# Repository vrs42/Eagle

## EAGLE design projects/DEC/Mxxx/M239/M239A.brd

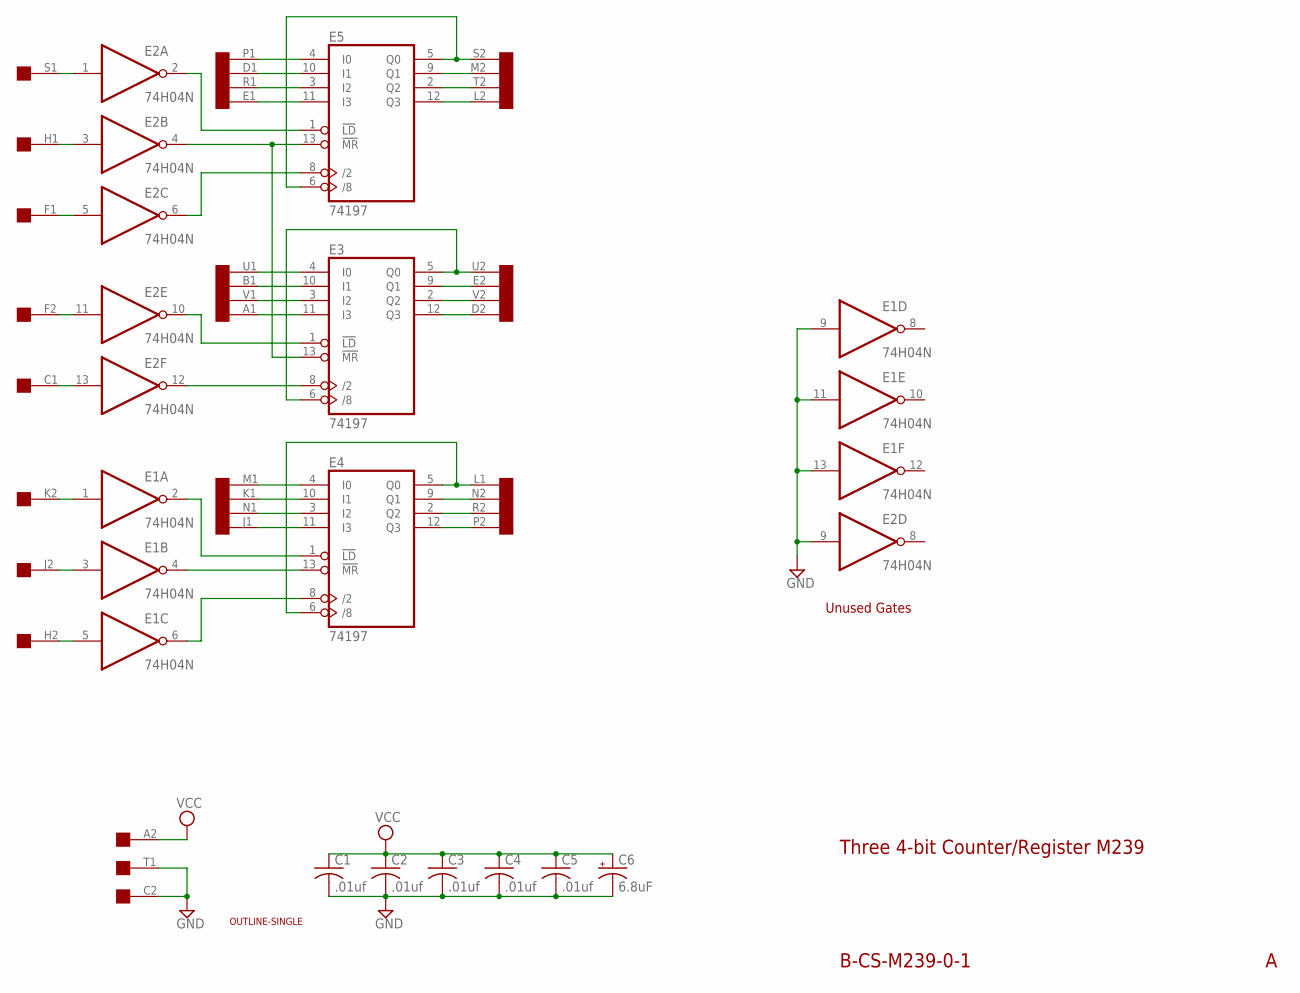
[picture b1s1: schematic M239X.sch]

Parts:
C1, C2, C3, C4, C5: .01uf; C050-025X075
C6: 6.8uF; E22-6
E1, E2: 74H04N; DIL14
E3, E4, E5: 74197; DIL14
U$1: OUTLINE-SINGLE; SINGLE
U$4: SINGLE; EDGE-CON2

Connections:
GND: C1.2, C2.2, C3.2, C4.2, C5.2, C6.-, E1.7 (GND), E1.9 (I), E1.11 (I), E1.13 (I), E2.7 (GND), E2.9 (I), E3.7 (GND), E4.7 (GND), E5.7 (GND), U$4.C2, U$4.T1
unnamed: E5.4 (I0), U$4.P1
unnamed: E5.10 (I1), U$4.D1
unnamed: E5.3 (I2), U$4.R1
unnamed: E5.11 (I3), U$4.E1
unnamed: E5.5 (Q0), E5.6 (/8), U$4.S2
unnamed: E2.2 (O), E5.1 (!LD)
unnamed: E2.4 (O), E3.13 (!MR), E5.13 (!MR)
unnamed: E2.6 (O), E5.8 (/2)
unnamed: E2.1 (I), U$4.S1
unnamed: E2.3 (I), U$4.H1
unnamed: E2.5 (I), U$4.F1
unnamed: E2.10 (O), E3.1 (!LD)
unnamed: E2.12 (O), E3.8 (/2)
unnamed: E3.5 (Q0), E3.6 (/8), U$4.U2
unnamed: E2.11 (I), U$4.F2
unnamed: E2.13 (I), U$4.C1
unnamed: E3.11 (I3), U$4.A1
unnamed: E3.3 (I2), U$4.V1
unnamed: E3.10 (I1), U$4.B1
unnamed: E3.4 (I0), U$4.U1
unnamed: E5.9 (Q1), U$4.M2
unnamed: E5.2 (Q2), U$4.T2
unnamed: E5.12 (Q3), U$4.L2
unnamed: E3.9 (Q1), U$4.E2
unnamed: E3.2 (Q2), U$4.V2
unnamed: E3.12 (Q3), U$4.D2
unnamed: E4.5 (Q0), E4.6 (/8), U$4.L1
unnamed: E1.4 (O), E4.13 (!MR)
unnamed: E1.6 (O), E4.8 (/2)
unnamed: E1.2 (O), E4.1 (!LD)
unnamed: E1.1 (I), U$4.K2
unnamed: E1.3 (I), U$4.J2
unnamed: E1.5 (I), U$4.H2
unnamed: E4.4 (I0), U$4.M1
unnamed: E4.10 (I1), U$4.K1
unnamed: E4.3 (I2), U$4.N1
unnamed: E4.11 (I3), U$4.J1
unnamed: E4.9 (Q1), U$4.N2
unnamed: E4.2 (Q2), U$4.R2
unnamed: E4.12 (Q3), U$4.P2
VCC: C1.1, C2.1, C3.1, C4.1, C5.1, C6.+, E1.14 (VCC), E2.14 (VCC), E3.14 (VCC), E4.14 (VCC), E5.14 (VCC), U$4.A2

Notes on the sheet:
B-CS-M239-0-1
Three 4-bit Counter/Register M239
Unused Gates

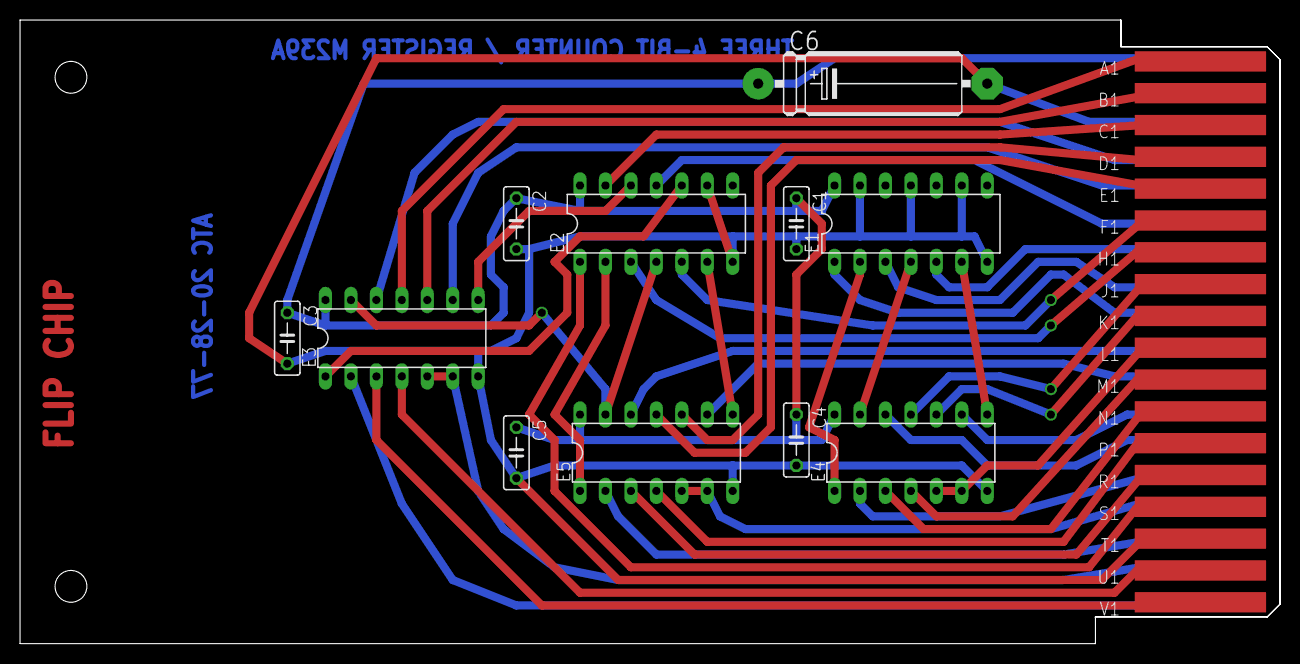
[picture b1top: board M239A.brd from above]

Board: 2 copper layers, 125.7 x 62.2 mm, 14 parts (0 on the bottom side), 42 nets.

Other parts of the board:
U$5: FLIPCHIP

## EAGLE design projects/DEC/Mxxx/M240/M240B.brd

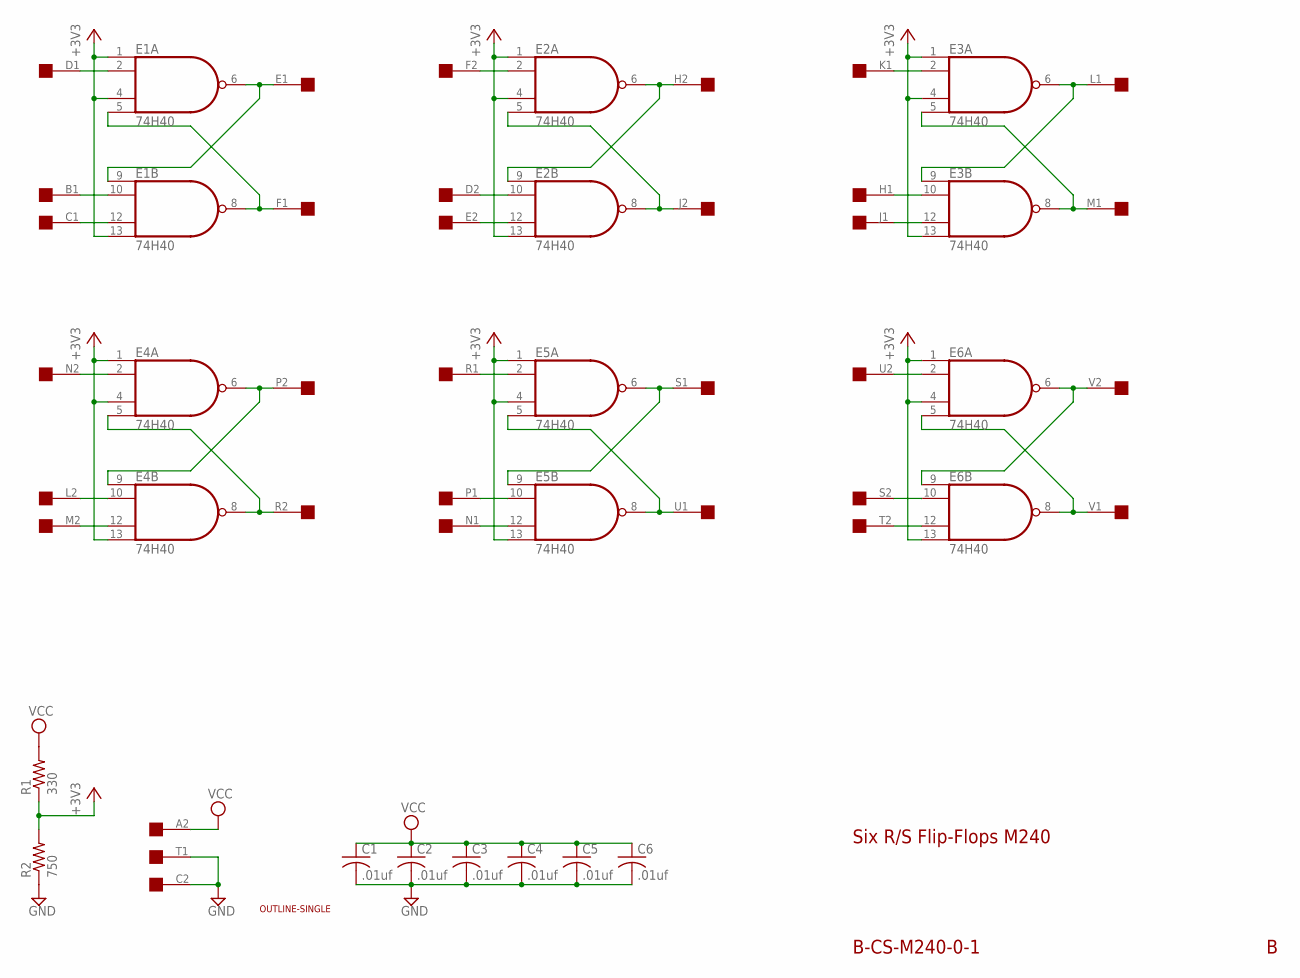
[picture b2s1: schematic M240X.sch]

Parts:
C1, C2, C3, C4, C5, C6: .01uf; C050-025X075
E1, E2, E3, E4, E5, E6: 74H40; DIL14
R1: 330; 0207/10
R2: 750; 0207/10
U$1: OUTLINE-SINGLE; SINGLE
U$4: SINGLE; EDGE-CON2

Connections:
+3V3: E1.1 (I0), E1.4 (I2), E1.13 (I3), E2.1 (I0), E2.4 (I2), E2.13 (I3), E3.1 (I0), E3.4 (I2), E3.13 (I3), E4.1 (I0), E4.4 (I2), E4.13 (I3), E5.1 (I0), E5.4 (I2), E5.13 (I3), E6.1 (I0), E6.4 (I2), E6.13 (I3), R1.1, R2.2
GND: C1.2, C2.2, C3.2, C4.2, C5.2, C6.2, E1.7 (GND), E2.7 (GND), E3.7 (GND), E4.7 (GND), E5.7 (GND), E6.7 (GND), R2.1, U$4.C2, U$4.T1
unnamed: E1.6 (O), E1.9 (I0), U$4.E1
unnamed: E1.5 (I3), E1.8 (O), U$4.F1
unnamed: E1.2 (I1), U$4.D1
unnamed: E1.10 (I1), U$4.B1
unnamed: E1.12 (I2), U$4.C1
unnamed: E2.6 (O), E2.9 (I0), U$4.H2
unnamed: E2.5 (I3), E2.8 (O), U$4.J2
unnamed: E2.2 (I1), U$4.F2
unnamed: E2.10 (I1), U$4.D2
unnamed: E2.12 (I2), U$4.E2
unnamed: E3.6 (O), E3.9 (I0), U$4.L1
unnamed: E3.5 (I3), E3.8 (O), U$4.M1
unnamed: E3.2 (I1), U$4.K1
unnamed: E3.10 (I1), U$4.H1
unnamed: E3.12 (I2), U$4.J1
unnamed: E4.6 (O), E4.9 (I0), U$4.P2
unnamed: E4.5 (I3), E4.8 (O), U$4.R2
unnamed: E4.2 (I1), U$4.N2
unnamed: E4.10 (I1), U$4.L2
unnamed: E4.12 (I2), U$4.M2
unnamed: E5.6 (O), E5.9 (I0), U$4.S1
unnamed: E5.5 (I3), E5.8 (O), U$4.U1
unnamed: E5.2 (I1), U$4.R1
unnamed: E5.10 (I1), U$4.P1
unnamed: E5.12 (I2), U$4.N1
unnamed: E6.6 (O), E6.9 (I0), U$4.V2
unnamed: E6.5 (I3), E6.8 (O), U$4.V1
unnamed: E6.2 (I1), U$4.U2
unnamed: E6.10 (I1), U$4.S2
unnamed: E6.12 (I2), U$4.T2
VCC: C1.1, C2.1, C3.1, C4.1, C5.1, C6.1, E1.14 (VCC), E2.14 (VCC), E3.14 (VCC), E4.14 (VCC), E5.14 (VCC), E6.14 (VCC), R1.2, U$4.A2

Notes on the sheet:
B-CS-M240-0-1
Six R/S Flip-Flops M240

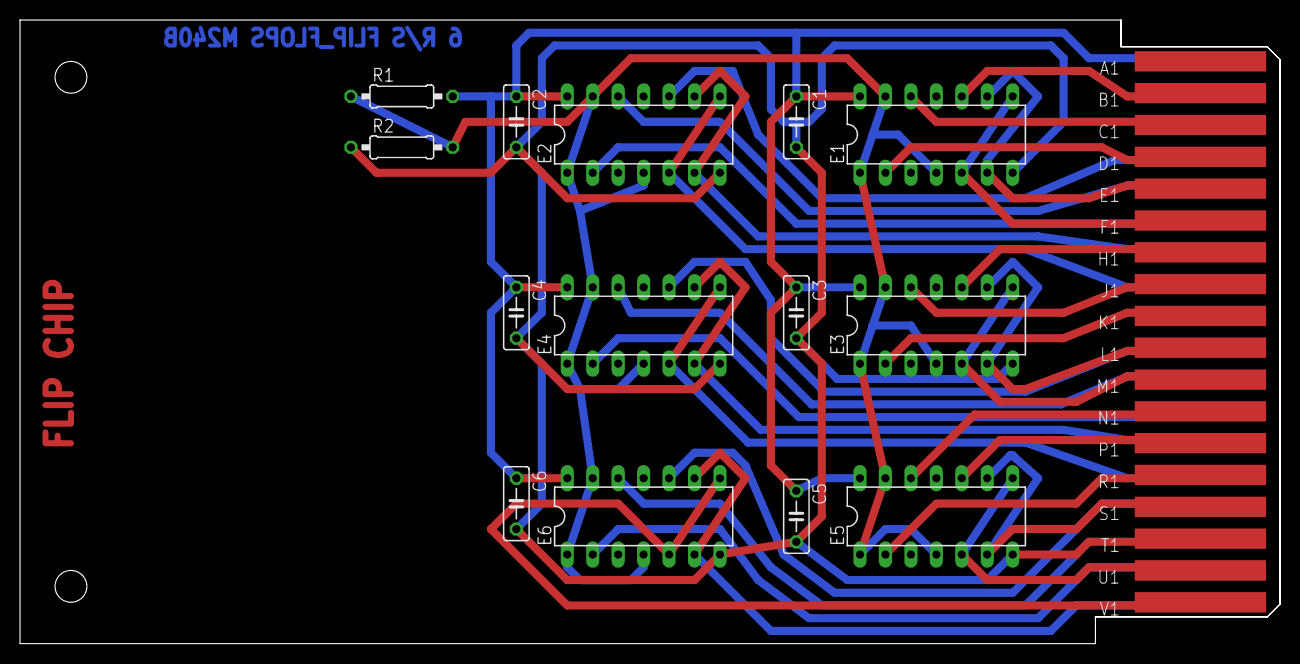
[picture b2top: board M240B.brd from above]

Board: 2 copper layers, 125.7 x 62.2 mm, 17 parts (0 on the bottom side), 33 nets.

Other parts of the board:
U$5: FLIPCHIP

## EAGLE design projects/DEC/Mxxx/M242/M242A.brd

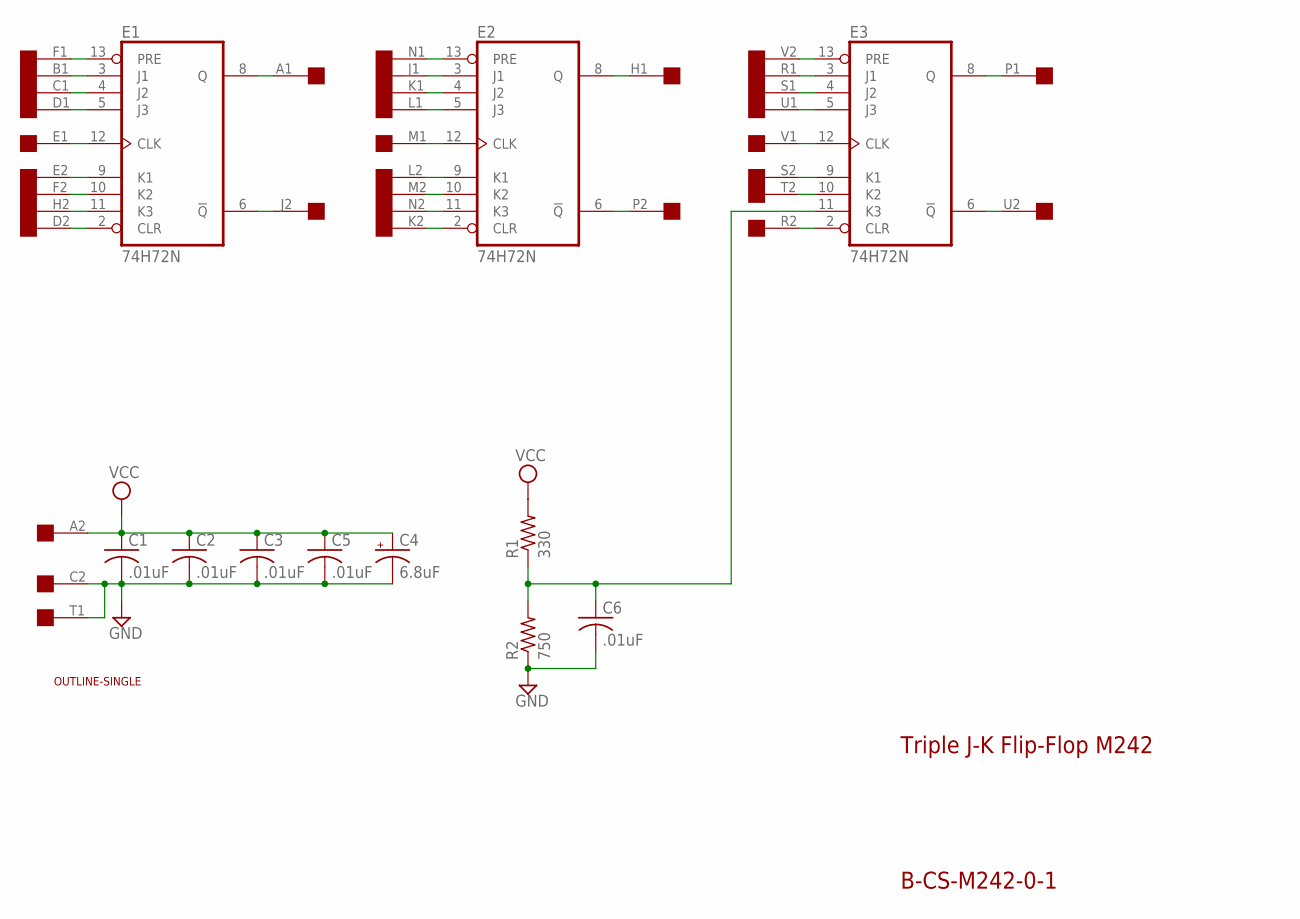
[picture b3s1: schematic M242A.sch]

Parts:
C1, C2, C3, C5, C6: .01uF; C050-025X075
C4: 6.8uF; E12-8
E1, E2, E3: 74H72N; DIL14
R1: 330; 0207/10
R2: 750; 0207/10
U$1: OUTLINE-SINGLE; SINGLE
U$2: SINGLE; EDGE-CON2

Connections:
A1: E1.8 (Q), U$2.A1
B1: E1.3 (J1), U$2.B1
C1: E1.4 (J2), U$2.C1
D1: E1.5 (J3), U$2.D1
D2: E1.2 (CLR), U$2.D2
E1: E1.12 (CLK), U$2.E1
E2: E1.9 (K1), U$2.E2
F1: E1.13 (PRE), U$2.F1
F2: E1.10 (K2), U$2.F2
GND: C1.2, C2.2, C3.2, C4.-, C5.2, C6.2, E1.7 (GND), E2.7 (GND), E3.7 (GND), R2.1, U$2.C2, U$2.T1
H1: E2.8 (Q), U$2.H1
H2: E1.11 (K3), U$2.H2
J1: E2.3 (J1), U$2.J1
J2: E1.6 (!Q), U$2.J2
K1: E2.4 (J2), U$2.K1
K2: E2.2 (CLR), U$2.K2
L1: E2.5 (J3), U$2.L1
L2: E2.9 (K1), U$2.L2
M1: E2.12 (CLK), U$2.M1
M2: E2.10 (K2), U$2.M2
N1: E2.13 (PRE), U$2.N1
N2: E2.11 (K3), U$2.N2
unnamed: C6.1, E3.11 (K3), R1.1, R2.2
P1: E3.8 (Q), U$2.P1
P2: E2.6 (!Q), U$2.P2
R1: E3.3 (J1), U$2.R1
R2: E3.2 (CLR), U$2.R2
S1: E3.4 (J2), U$2.S1
S2: E3.9 (K1), U$2.S2
T2: E3.10 (K2), U$2.T2
U1: E3.5 (J3), U$2.U1
U2: E3.6 (!Q), U$2.U2
V1: E3.12 (CLK), U$2.V1
V2: E3.13 (PRE), U$2.V2
VCC: C1.1, C2.1, C3.1, C4.+, C5.1, E1.14 (VCC), E2.14 (VCC), E3.14 (VCC), R1.2, U$2.A2

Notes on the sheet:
Triple J-K Flip-Flop M242
B-CS-M242-0-1

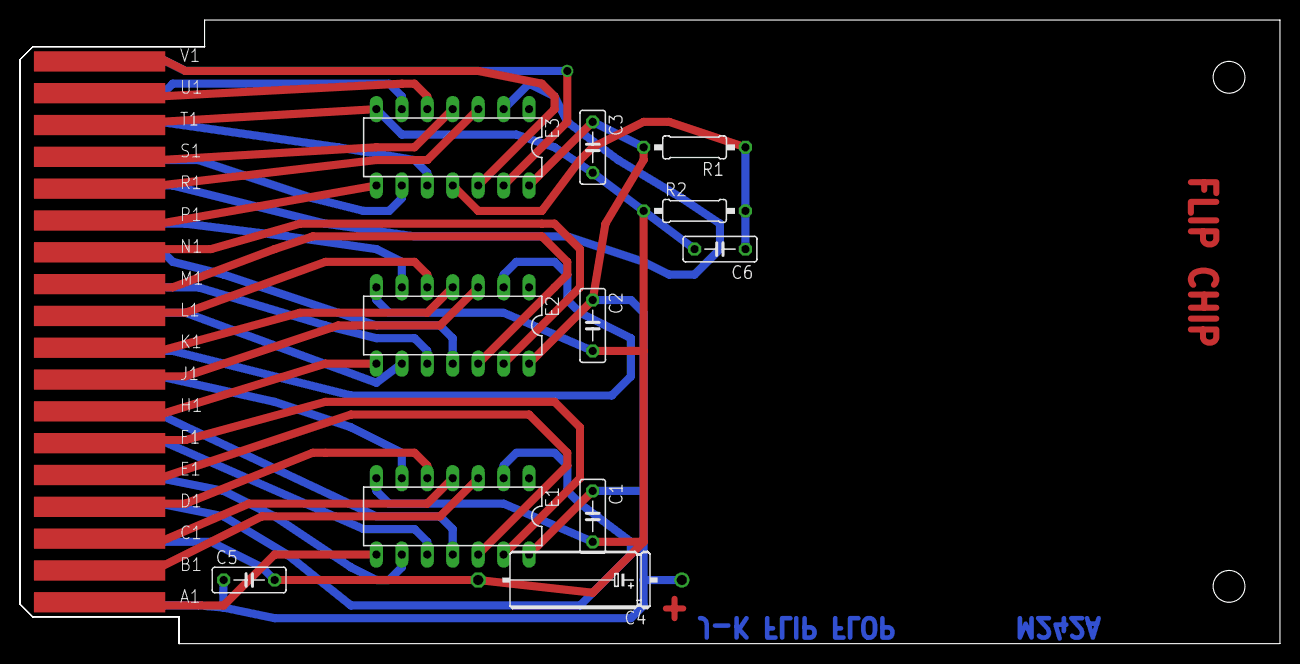
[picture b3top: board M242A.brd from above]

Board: 2 copper layers, 125.7 x 62.2 mm, 13 parts (0 on the bottom side), 35 nets.

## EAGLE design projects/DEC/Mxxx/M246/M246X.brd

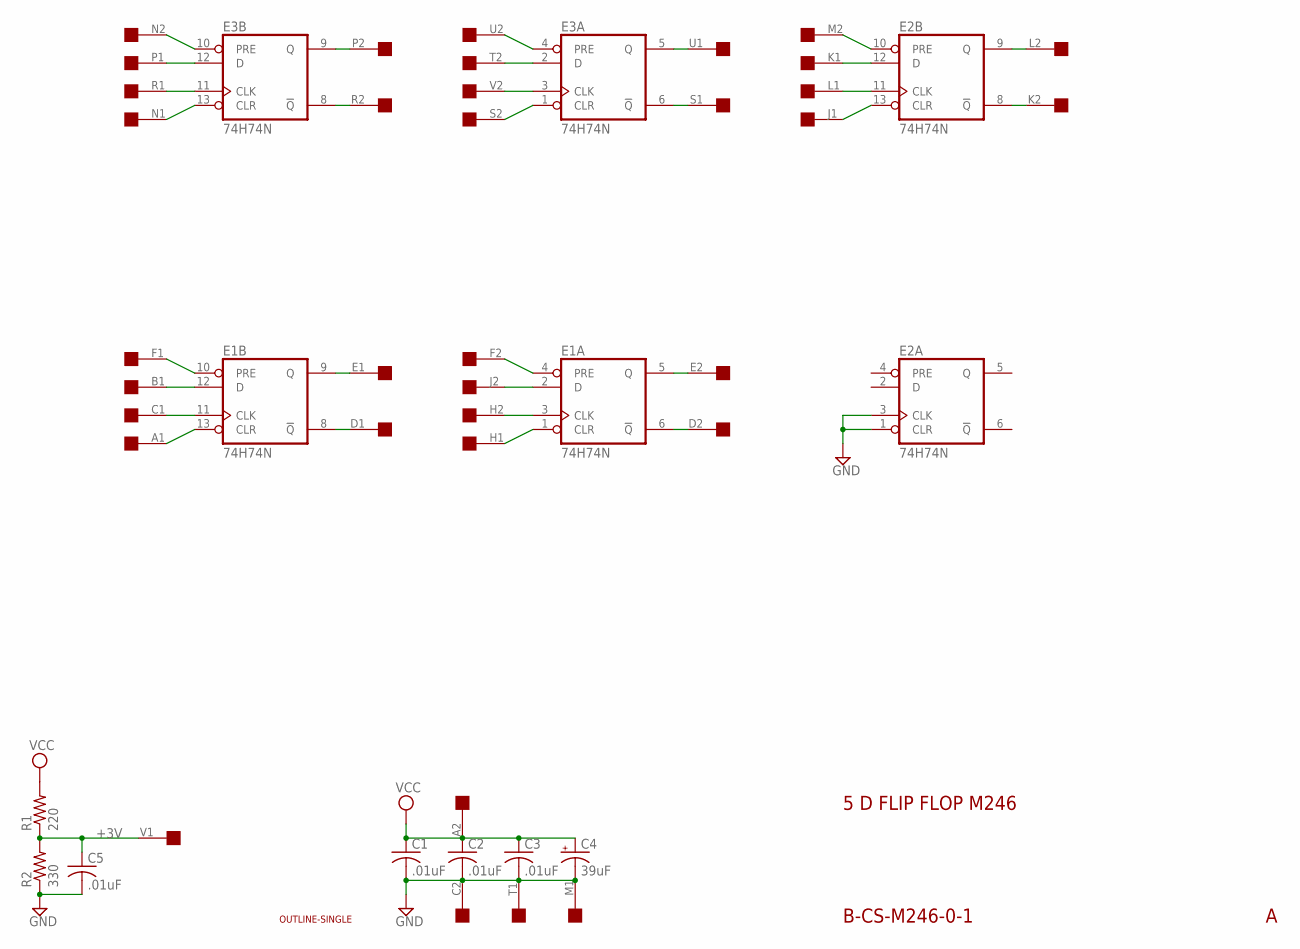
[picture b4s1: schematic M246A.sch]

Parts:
C1, C2, C3, C5: .01uF; C050-025X075
C4: 39uF; E12-8
E1, E2, E3: 74H74N; DIL14
R1: 220; 0207/10
R2: 330; 0207/10
U$1: OUTLINE-SINGLE; SINGLE
U$2: EDGE-2CONNECTOR; EDGE-CON2

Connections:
+3V: C5.1, R1.1, R2.2, U$2.V1
GND: C1.2, C2.2, C3.2, C4.-, C5.2, E1.7 (GND), E2.1 (CLR), E2.3 (CLK), E2.7 (GND), E3.7 (GND), R2.1, U$2.C2, U$2.M1, U$2.T1
unnamed: E3.5 (Q), U$2.U1
unnamed: E1.6 (!Q), U$2.D2
unnamed: E1.5 (Q), U$2.E2
unnamed: E1.2 (D), U$2.J2
unnamed: E1.4 (PRE), U$2.F2
unnamed: E1.3 (CLK), U$2.H2
unnamed: E1.1 (CLR), U$2.H1
unnamed: E3.1 (CLR), U$2.S2
unnamed: E3.3 (CLK), U$2.V2
unnamed: E3.8 (!Q), U$2.R2
unnamed: E3.9 (Q), U$2.P2
unnamed: E3.4 (PRE), U$2.U2
unnamed: E3.2 (D), U$2.T2
unnamed: E2.13 (CLR), U$2.J1
unnamed: E2.11 (CLK), U$2.L1
unnamed: E2.12 (D), U$2.K1
unnamed: E2.8 (!Q), U$2.K2
unnamed: E2.9 (Q), U$2.L2
unnamed: E2.10 (PRE), U$2.M2
unnamed: E1.13 (CLR), U$2.A1
unnamed: E1.11 (CLK), U$2.C1
unnamed: E1.10 (PRE), U$2.F1
unnamed: E1.8 (!Q), U$2.D1
unnamed: E1.9 (Q), U$2.E1
unnamed: E1.12 (D), U$2.B1
unnamed: E3.13 (CLR), U$2.N1
unnamed: E3.11 (CLK), U$2.R1
unnamed: E3.12 (D), U$2.P1
unnamed: E3.10 (PRE), U$2.N2
unnamed: E3.6 (!Q), U$2.S1
VCC: C1.1, C2.1, C3.1, C4.+, E1.14 (VCC), E2.14 (VCC), E3.14 (VCC), R1.2, U$2.A2

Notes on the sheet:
B-CS-M246-0-1
5 D FLIP FLOP M246

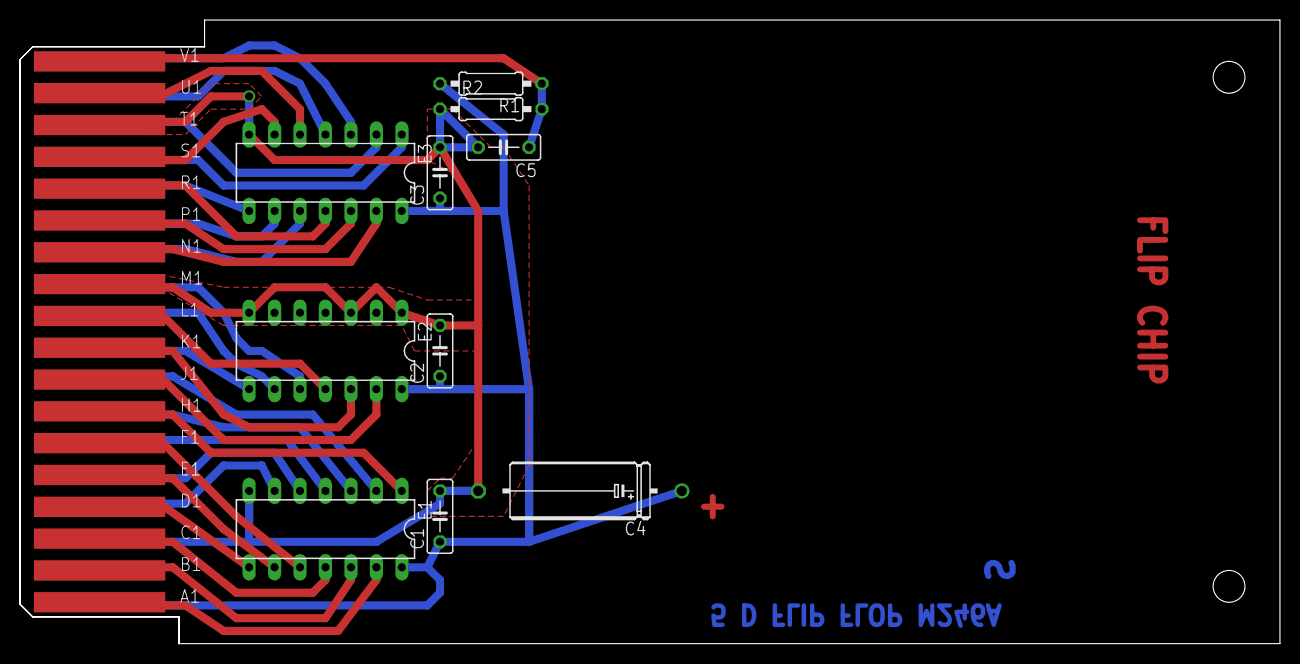
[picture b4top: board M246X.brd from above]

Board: 2 copper layers, 125.7 x 62.2 mm, 12 parts (0 on the bottom side), 33 nets.

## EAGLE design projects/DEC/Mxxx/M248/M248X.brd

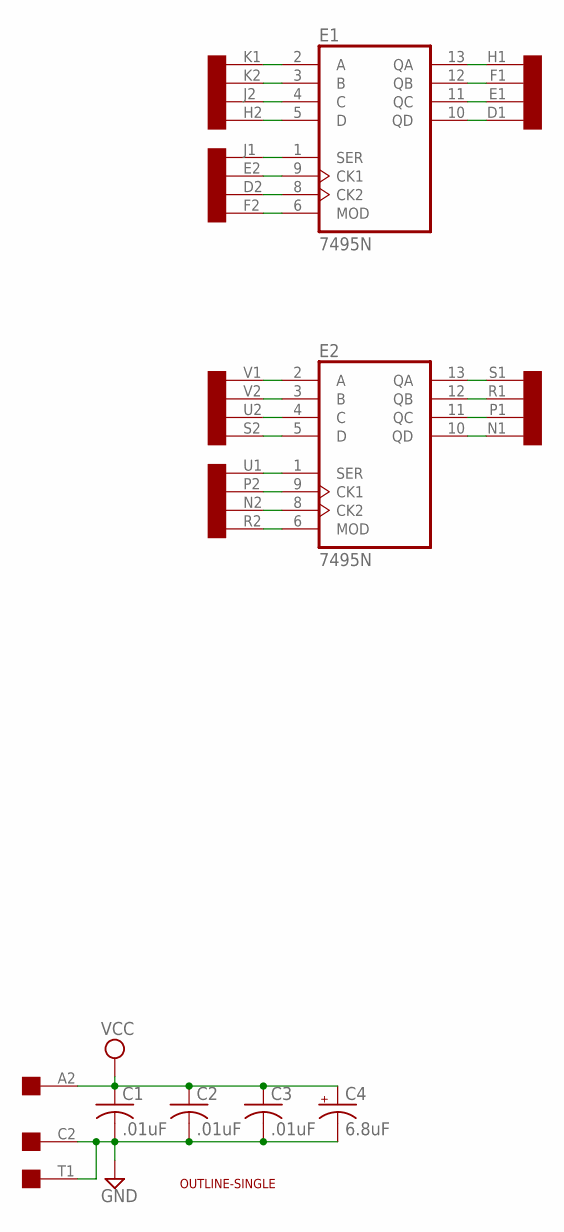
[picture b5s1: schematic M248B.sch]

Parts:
C1, C2, C3: .01uF; C050-025X075
C4: 6.8uF; E12-8
E1, E2: 7495N; DIL14
U$1: OUTLINE-SINGLE; SINGLE
U$2: SINGLE; EDGE-CON2

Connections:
GND: C1.2, C2.2, C3.2, C4.-, E1.7 (GND), E2.7 (GND), U$2.C2, U$2.T1
unnamed: E1.1 (SER), U$2.J1
unnamed: E1.2 (A), U$2.K1
unnamed: E1.3 (B), U$2.K2
unnamed: E1.4 (C), U$2.J2
unnamed: E1.5 (D), U$2.H2
unnamed: E1.6 (MOD), U$2.F2
unnamed: E1.8 (CK2), U$2.D2
unnamed: E1.9 (CK1), U$2.E2
unnamed: E1.10 (QD), U$2.D1
unnamed: E1.11 (QC), U$2.E1
unnamed: E1.12 (QB), U$2.F1
unnamed: E1.13 (QA), U$2.H1
unnamed: E2.1 (SER), U$2.U1
unnamed: E2.2 (A), U$2.V1
unnamed: E2.3 (B), U$2.V2
unnamed: E2.4 (C), U$2.U2
unnamed: E2.5 (D), U$2.S2
unnamed: E2.6 (MOD), U$2.R2
unnamed: E2.8 (CK2), U$2.N2
unnamed: E2.9 (CK1), U$2.P2
unnamed: E2.10 (QD), U$2.N1
unnamed: E2.11 (QC), U$2.P1
unnamed: E2.12 (QB), U$2.R1
unnamed: E2.13 (QA), U$2.S1
VCC: C1.1, C2.1, C3.1, C4.+, E1.14 (VCC), E2.14 (VCC), U$2.A2

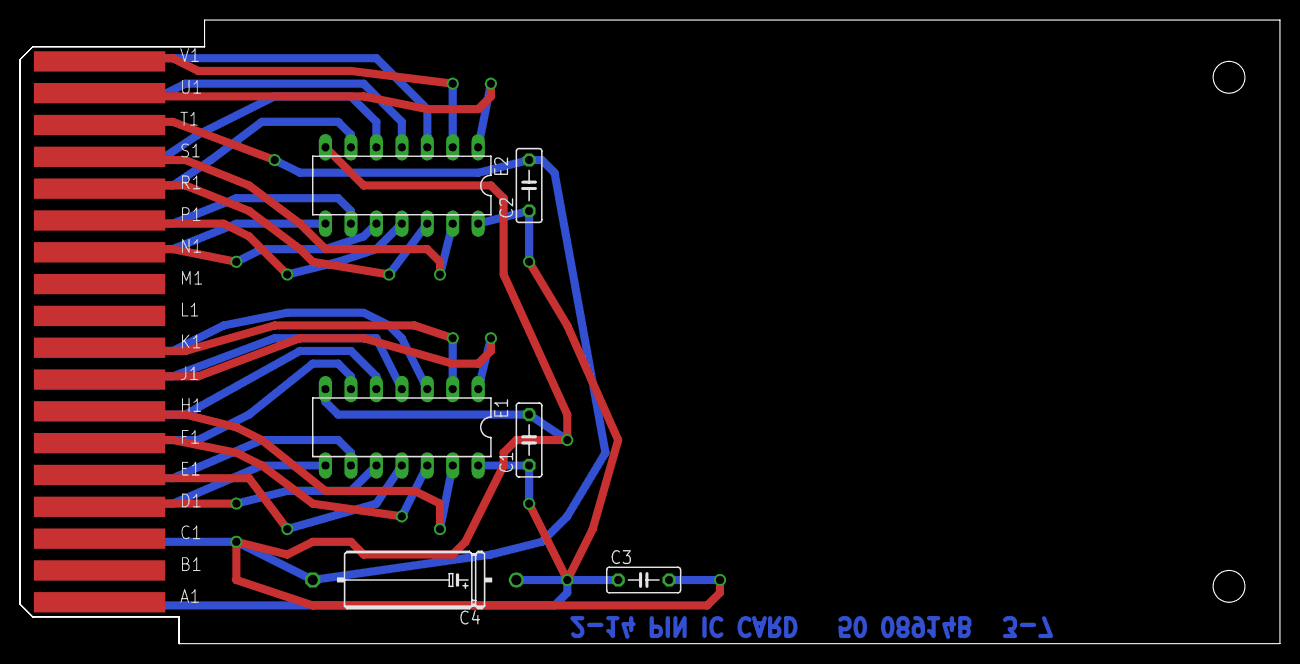
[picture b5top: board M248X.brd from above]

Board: 2 copper layers, 125.7 x 62.2 mm, 8 parts (0 on the bottom side), 26 nets.

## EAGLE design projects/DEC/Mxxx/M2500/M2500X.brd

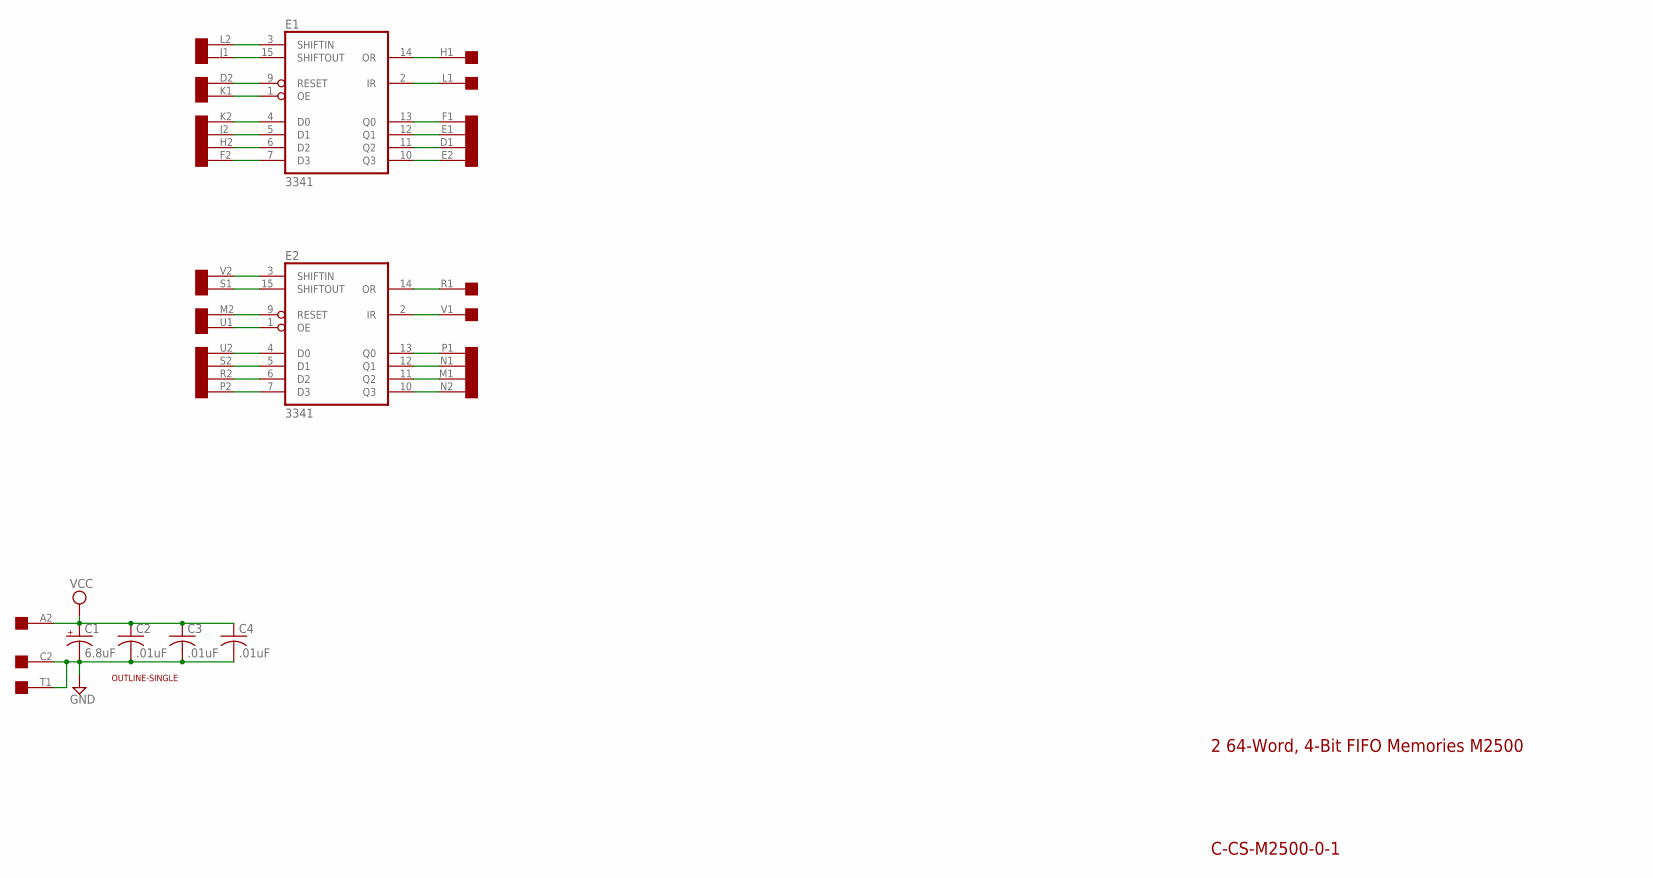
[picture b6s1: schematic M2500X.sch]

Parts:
C1: 6.8uF; E12-8
C2, C3, C4: .01uF; C050-025X075
E1, E2: 3341; DIL16
U$1: OUTLINE-SINGLE; SINGLE
U$2: SINGLE; EDGE-CON2

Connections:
D1: E1.11 (Q2), U$2.D1
D2: E1.9 (RESET), U$2.D2
E1: E1.12 (Q1), U$2.E1
E2: E1.10 (Q3), U$2.E2
F1: E1.13 (Q0), U$2.F1
F2: E1.7 (D3), U$2.F2
GND: C1.-, C2.2, C3.2, C4.2, E1.8 (GND), E2.8 (GND), U$2.C2, U$2.T1
H1: E1.14 (OR), U$2.H1
H2: E1.6 (D2), U$2.H2
J1: E1.15 (SHIFTOUT), U$2.J1
J2: E1.5 (D1), U$2.J2
K1: E1.1 (OE), U$2.K1
K2: E1.4 (D0), U$2.K2
L1: E1.2 (IR), U$2.L1
L2: E1.3 (SHIFTIN), U$2.L2
M1: E2.11 (Q2), U$2.M1
M2: E2.9 (RESET), U$2.M2
N1: E2.12 (Q1), U$2.N1
N2: E2.10 (Q3), U$2.N2
P1: E2.13 (Q0), U$2.P1
P2: E2.7 (D3), U$2.P2
R1: E2.14 (OR), U$2.R1
R2: E2.6 (D2), U$2.R2
S1: E2.15 (SHIFTOUT), U$2.S1
S2: E2.5 (D1), U$2.S2
U1: E2.1 (OE), U$2.U1
U2: E2.4 (D0), U$2.U2
V1: E2.2 (IR), U$2.V1
V2: E2.3 (SHIFTIN), U$2.V2
VCC: C1.+, C2.1, C3.1, C4.1, E1.16 (VCC), E2.16 (VCC), U$2.A2

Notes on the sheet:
C-CS-M2500-0-1
2 64-Word, 4-Bit FIFO Memories M2500

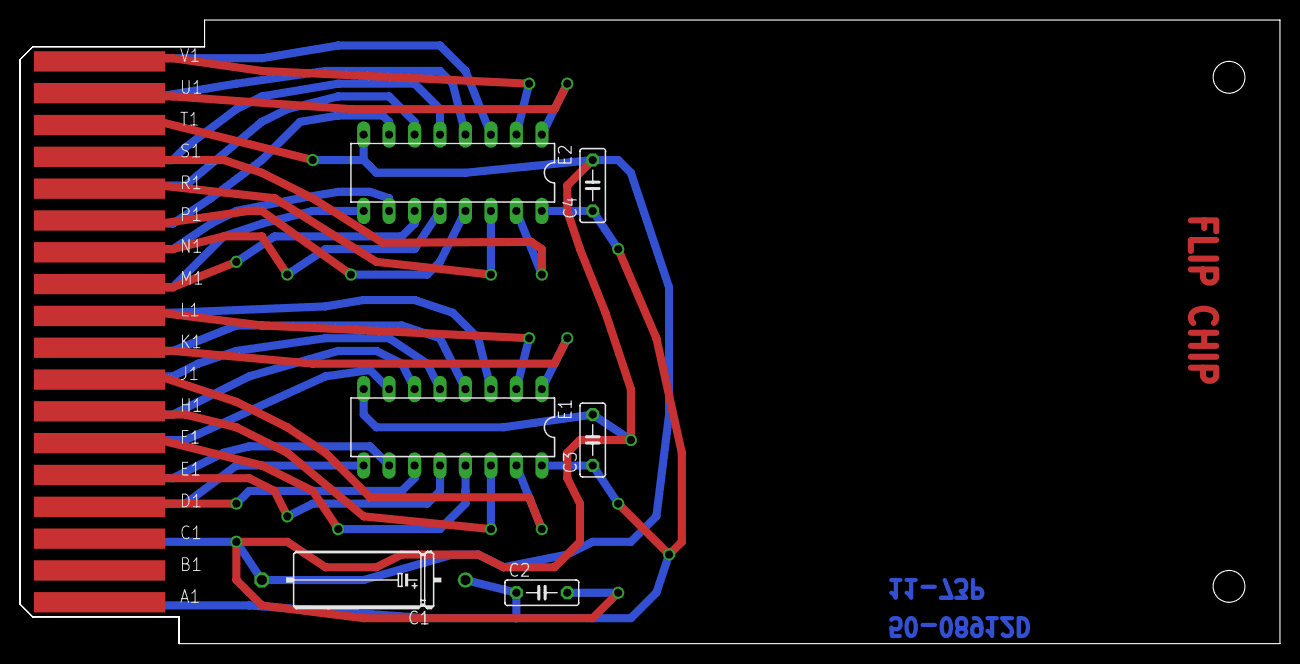
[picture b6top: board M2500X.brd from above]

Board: 2 copper layers, 125.7 x 62.2 mm, 8 parts (0 on the bottom side), 30 nets.

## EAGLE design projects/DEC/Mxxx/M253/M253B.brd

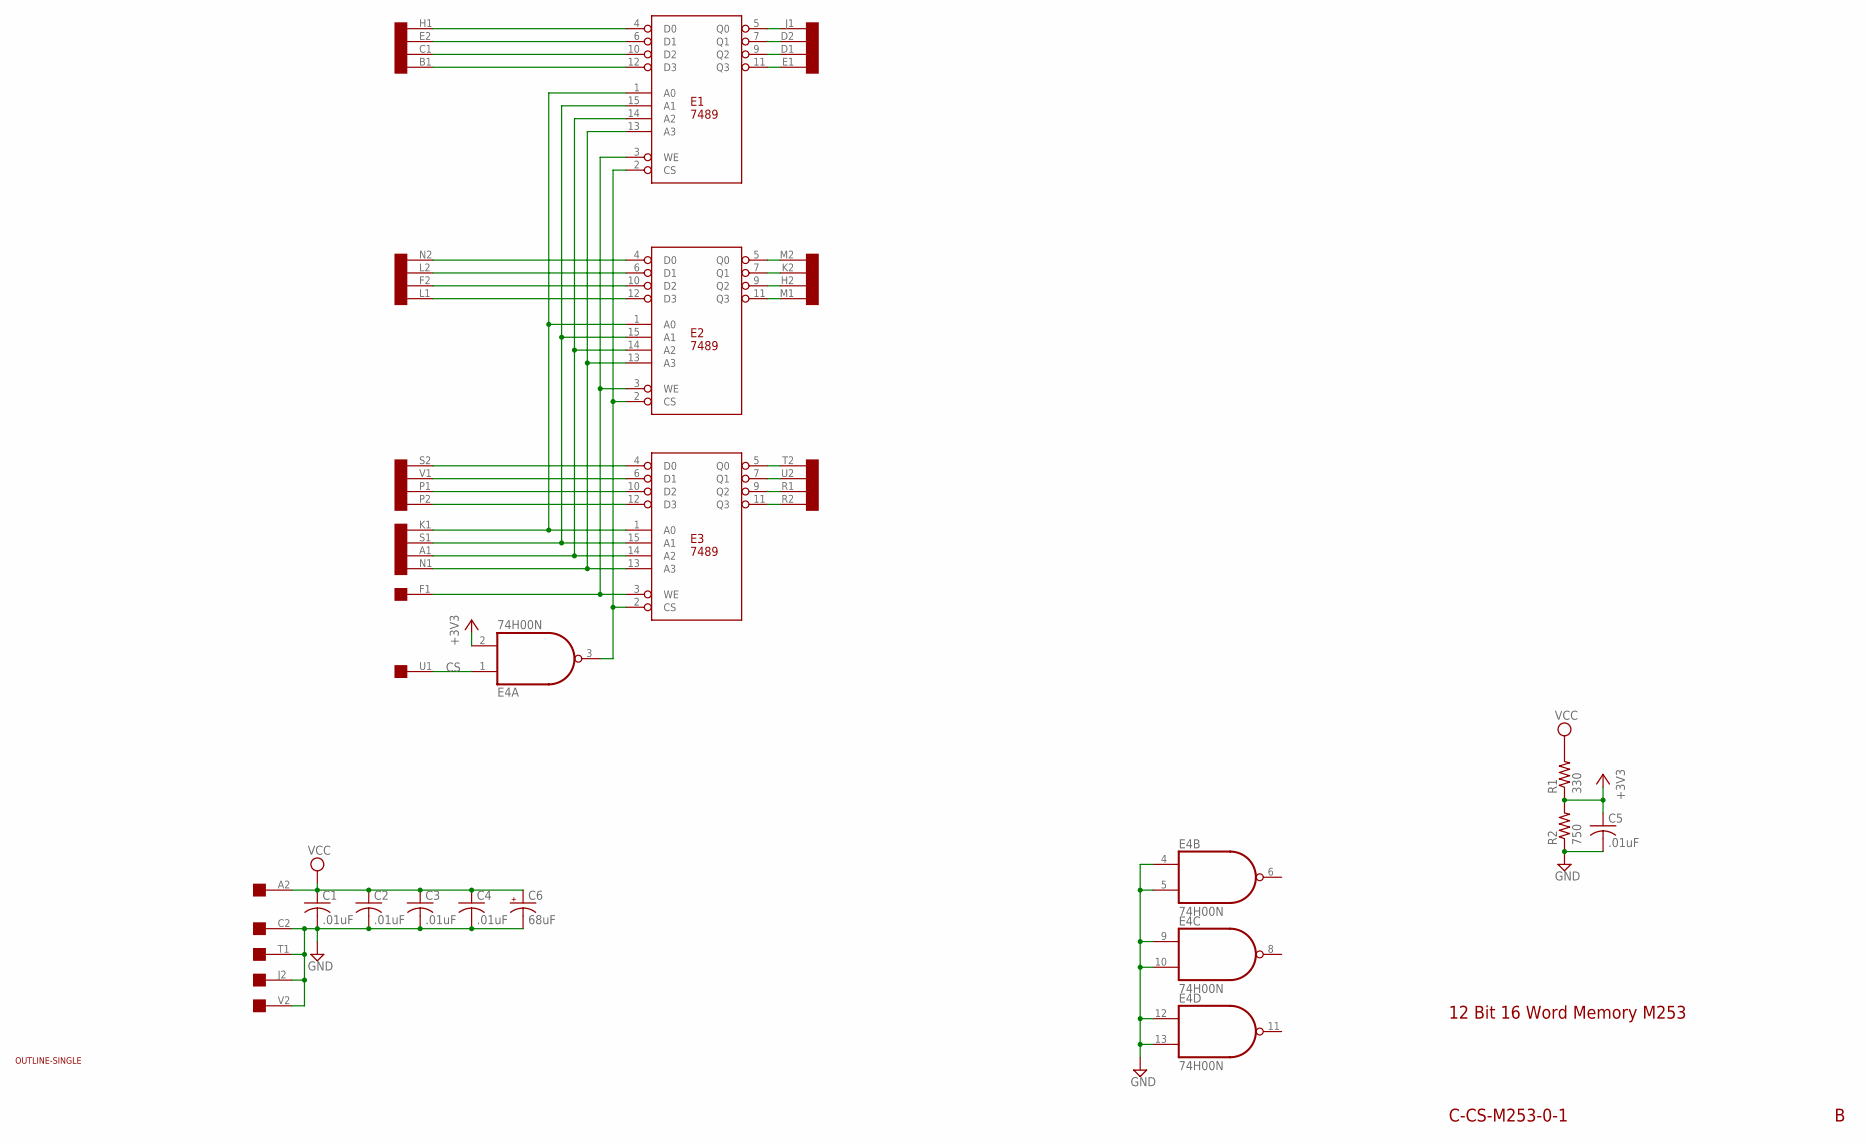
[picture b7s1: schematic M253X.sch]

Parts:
C1, C2, C3, C4, C5: .01uF; C050-025X075
C6: 68uF; E25-9
E1, E2, E3: 7489; DIL16
E4: 74H00N; DIL14
R1: 330; 0207/10
R2: 750; 0207/10
U$1: OUTLINE-SINGLE; SINGLE
U$2: SINGLE; EDGE-CON2

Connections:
+3V3: C5.1, E4.2 (I1), R1.1, R2.2
CS: E4.1 (I0), U$2.U1
GND: C1.2, C2.2, C3.2, C4.2, C5.2, C6.-, E1.8 (GND), E2.8 (GND), E3.8 (GND), E4.4 (I0), E4.5 (I1), E4.7 (GND), E4.9 (I0), E4.10 (I1), E4.12 (I0), E4.13 (I1), R2.1, U$2.C2, U$2.J2, U$2.T1, U$2.V2
unnamed: E1.2 (CS), E2.2 (CS), E3.2 (CS), E4.3 (O)
unnamed: E1.1 (A0), E2.1 (A0), E3.1 (A0), U$2.K1
unnamed: E1.14 (A2), E2.14 (A2), E3.14 (A2), U$2.A1
unnamed: E1.13 (A3), E2.13 (A3), E3.13 (A3), U$2.N1
unnamed: E1.3 (WE), E2.3 (WE), E3.3 (WE), U$2.F1
unnamed: E1.15 (A1), E2.15 (A1), E3.15 (A1), U$2.S1
unnamed: E1.6 (D1), U$2.E2
unnamed: E1.4 (D0), U$2.H1
unnamed: E1.10 (D2), U$2.C1
unnamed: E1.12 (D3), U$2.B1
unnamed: E2.6 (D1), U$2.L2
unnamed: E2.4 (D0), U$2.N2
unnamed: E2.10 (D2), U$2.F2
unnamed: E2.12 (D3), U$2.L1
unnamed: E3.12 (D3), U$2.P2
unnamed: E3.4 (D0), U$2.S2
unnamed: E3.10 (D2), U$2.P1
unnamed: E3.6 (D1), U$2.V1
unnamed: E1.7 (Q1), U$2.D2
unnamed: E1.5 (Q0), U$2.J1
unnamed: E1.11 (Q3), U$2.E1
unnamed: E1.9 (Q2), U$2.D1
unnamed: E2.5 (Q0), U$2.M2
unnamed: E2.7 (Q1), U$2.K2
unnamed: E2.9 (Q2), U$2.H2
unnamed: E2.11 (Q3), U$2.M1
unnamed: E3.11 (Q3), U$2.R2
unnamed: E3.5 (Q0), U$2.T2
unnamed: E3.7 (Q1), U$2.U2
unnamed: E3.9 (Q2), U$2.R1
VCC: C1.1, C2.1, C3.1, C4.1, C6.+, E1.16 (VCC), E2.16 (VCC), E3.16 (VCC), E4.14 (VCC), R1.2, U$2.A2

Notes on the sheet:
12 Bit 16 Word Memory M253
C-CS-M253-0-1

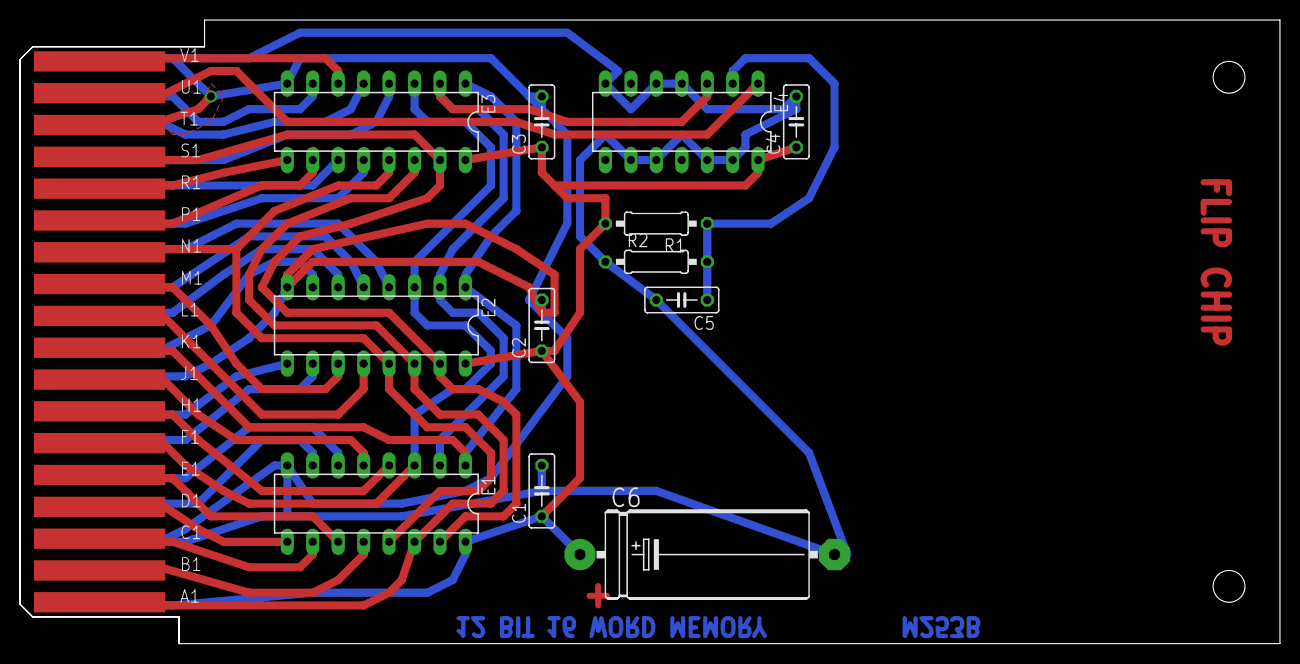
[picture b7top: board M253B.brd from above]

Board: 2 copper layers, 125.7 x 62.2 mm, 14 parts (0 on the bottom side), 34 nets.
